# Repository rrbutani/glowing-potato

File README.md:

# glowing-potato

A work in progress. Still needs a name and a README.

##### Group

The group behind this project consists of:
 - [Blake Martini](https://github.com/Dreadzone345)
 - [Sneha Pendharker](https://github.com/spendharkar)
 - [Sameer Mithani](https://github.com/sameermithani)
 - [Rahul Butani](https://github.com/rrbutani)

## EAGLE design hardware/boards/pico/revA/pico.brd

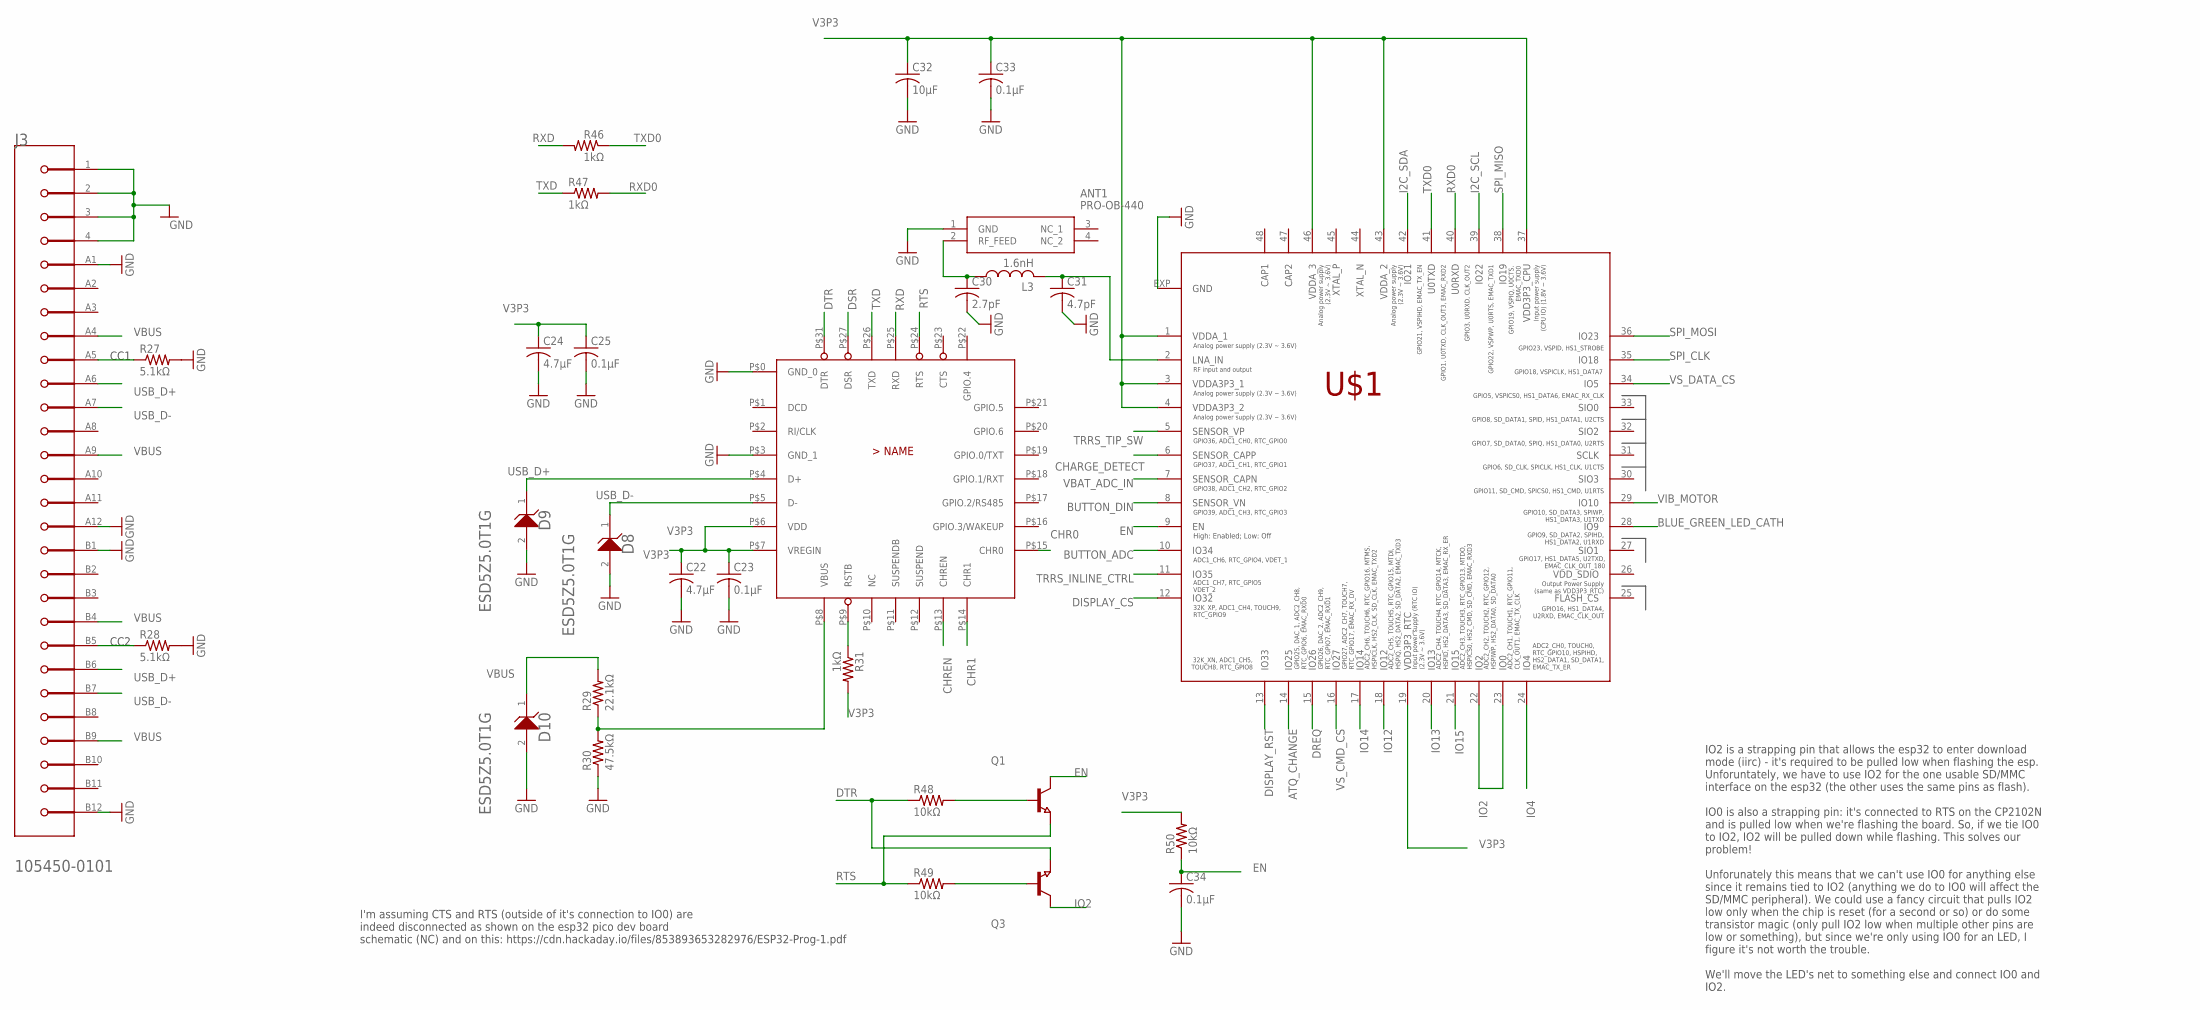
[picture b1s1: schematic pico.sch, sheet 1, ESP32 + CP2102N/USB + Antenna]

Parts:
ANT1: PRO-OB-440; PRO-OB-440_1
C22, C24: 4.7μF; C0402
C23, C25, C33, C34: 0.1μF; C0402
C30: 2.7pF; C0402
C31: 4.7pF; C0402
C32: 10μF; C0402
D8, D9, D10: ON_SEMICONDUCTOR_ESD5Z5.0T1GON_SEMICONDUCTOR_ESD5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; ON_SEMICONDUCTOR_ESD5Z5.0T1G_0
J3: MOLEX_105450-0101MOLEX_105450-0101_0_0; MOLEX_105450-0101_0
JL: CP2102N-A02-GQFN28; QFN28
L3: 1.6nH; R0402
Q1, Q3: NPN-TRANSISTOR_SOT23; SOT23
R27, R28: 5.1kΩ; R0402
R29: 22.1kΩ; R0402
R30: 47.5kΩ; R0402
R31, R46, R47: 1kΩ; R0402
R48, R49, R50: 10kΩ; R0402
U$1: ESP32-PICO-D4; QFN48

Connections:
ATQ_CHANGE: U$1.14 (IO25); also elsewhere on the board
BLUE_GREEN_LED_CATH: U$1.28 (IO9); also elsewhere on the board
BUTTON_ADC: U$1.10 (IO34); also elsewhere on the board
BUTTON_DIN: U$1.8 (SENSOR_VN); also elsewhere on the board
CHARGE_DETECT: U$1.6 (SENSOR_CAPP); also elsewhere on the board
CHR0: JL.P$15 (CHR0)
CHR1: JL.P$14 (CHR1)
CHREN: JL.P$13 (CHREN)
CP_RSTB: JL.P$9 (RSTB), R31.1
DISPLAY_CS: U$1.12 (IO32); also elsewhere on the board
DISPLAY_RST: U$1.13 (IO33); also elsewhere on the board
DREQ: U$1.15 (IO26); also elsewhere on the board
DSR: JL.P$27 (DSR)
DTR: JL.P$31 (DTR), Q3.2 (E), R48.1
EN: C34.1, Q1.3 (C), R50.1, U$1.9 (EN)
GND: ANT1.1 (GND), C22.2, C23.2, C24.2, C25.2, C30.2, C31.2, C32.2, C33.2, C34.2, D8.2 (A), D9.2 (A), D10.2 (A), J3.1 (MNT_1), J3.2 (MNT_2), J3.3 (MNT_3), J3.4 (MNT_4), J3.A1 (1_GND), J3.A12 (2_GND), J3.B1 (3_GND), J3.B12 (4_GND), JL.P$0 (GND_0), JL.P$3 (GND_1), R27.2, R28.2, R30.1, U$1.EXP (GND); also elsewhere on the board
I2C_SCL: U$1.39 (IO22); also elsewhere on the board
I2C_SDA: U$1.42 (IO21); also elsewhere on the board
IO2: Q3.3 (C), U$1.22 (IO2), U$1.23 (IO0); also elsewhere on the board
IO4: U$1.24 (IO4); also elsewhere on the board
IO12: U$1.18 (IO12); also elsewhere on the board
IO13: U$1.20 (IO13); also elsewhere on the board
IO14: U$1.17 (IO14); also elsewhere on the board
IO15: U$1.21 (IO15); also elsewhere on the board
unnamed: ANT1.2 (RF_FEED), C30.1, L3.1
unnamed: C31.1, L3.2, U$1.2 (LNA_IN)
unnamed: J3.A5 (CC1), R27.1
unnamed: J3.B5 (CC2), R28.1
unnamed: JL.P$8 (VBUS), R29.1, R30.2
unnamed: Q1.1 (B), R48.2
unnamed: Q3.1 (B), R49.2
RTS: JL.P$24 (RTS), Q1.2 (E), R49.1
RXD: JL.P$25 (RXD), R46.2
RXD0: R47.2, U$1.40 (U0RXD)
SPI_CLK: U$1.35 (IO18); also elsewhere on the board
SPI_MISO: U$1.38 (IO19); also elsewhere on the board
SPI_MOSI: U$1.36 (IO23); also elsewhere on the board
TRRS_INLINE_CTRL: U$1.11 (IO35); also elsewhere on the board
TRRS_TIP_SW: U$1.5 (SENSOR_VP); also elsewhere on the board
TXD: JL.P$26 (TXD), R47.1
TXD0: R46.1, U$1.41 (U0TXD)
USB_D+: D9.1 (K), J3.A6 (1_D+), J3.B6 (2_D+), JL.P$4 (D+)
USB_D-: D8.1 (K), J3.A7 (1_D-), J3.B7 (2_D-), JL.P$5 (D-)
V3P3: C22.1, C23.1, C24.1, C25.1, C32.1, C33.1, JL.P$6 (VDD), JL.P$7 (VREGIN), R31.2, R50.2, U$1.1 (VDDA_1), U$1.3 (VDDA3P3_1), U$1.4 (VDDA3P3_2), U$1.19 (VDD3P3_RTC), U$1.37 (VDD3P3_CPU), U$1.43 (VDDA_2), U$1.46 (VDDA_3); also elsewhere on the board
VBAT_ADC_IN: U$1.7 (SENSOR_CAPN); also elsewhere on the board
VBUS: D10.1 (K), J3.A4 (1_VBUS), J3.A9 (2_VBUS), J3.B4 (3_VBUS), J3.B9 (4_VBUS), R29.2; also elsewhere on the board
VIB_MOTOR: U$1.29 (IO10); also elsewhere on the board
VS_CMD_CS: U$1.16 (IO27); also elsewhere on the board
VS_DATA_CS: U$1.34 (IO5); also elsewhere on the board

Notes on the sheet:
CC1
CC2
I'm assuming CTS and RTS (outside of it's connection to IO0) are indeed disconnected as shown on the esp32 pico dev board schematic (NC) and on this: https://cdn.hackaday.io/files/853893653282976/ESP32-Prog-1.pdf
IO2 is a strapping pin that allows the esp32 to enter download mode (iirc) - it's required to be pulled low when flashing the esp. Unforuntately, we have to use IO2 for the one usable SD/MMC interface on the esp32 (the other uses the same pins as flash). IO0 is also a strapping pin: it's connected 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

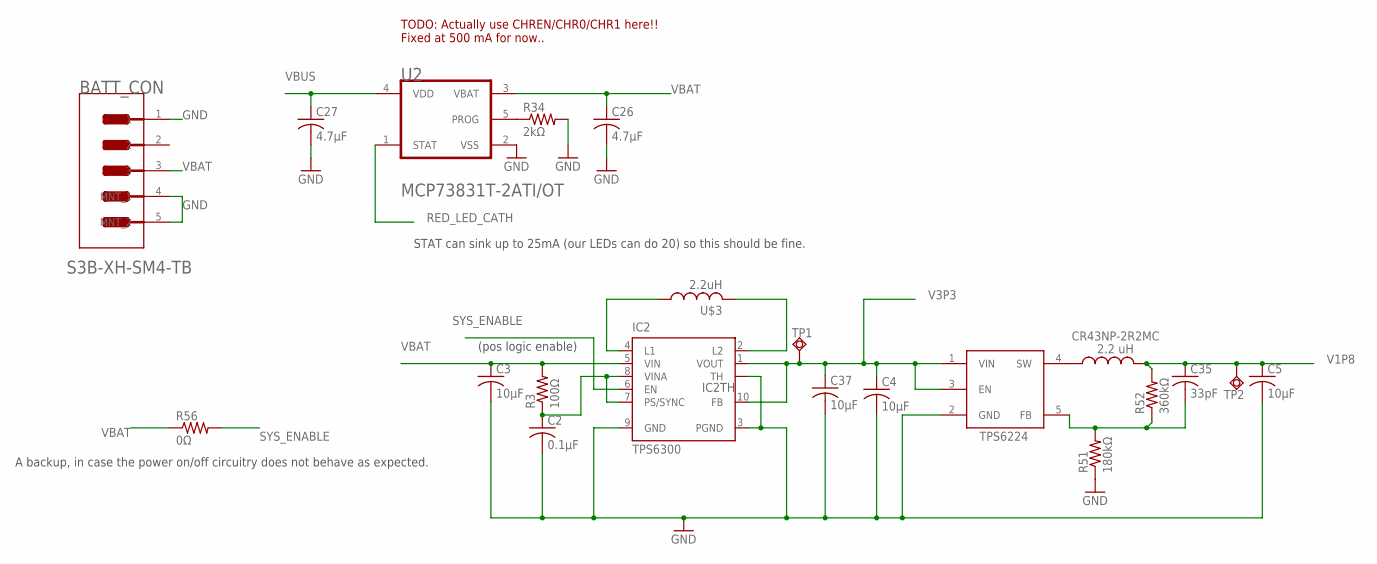
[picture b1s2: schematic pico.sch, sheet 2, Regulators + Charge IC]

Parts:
BATT_CON: JST_S3B-XH-SM4-TBJST_S3B-XH-SM4-TB_0_0; JST_S3B-XH-SM4-TB_0
C2: 0.1μF; C0402
C3, C4, C5, C37: 10μF; C0402
C26, C27: 4.7μF; C0402
C35: 33pF; C0402
IC2: TPS6300; DRC-S-PVSON-N10
R3: 100Ω; R0402
R34: 2kΩ; R0402
R51: 180kΩ; R0402
R52: 360kΩ; R0402
R56: 0Ω; R0603
TP1, TP2: TPSQTP15SQ; TP15SQ
TPS6224: TPS62240; TSP62240
U2: MICROCHIP_MCP73831T-2ATI-OTMICROCHIP_MCP73831T-2A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; MICROCHIP_MCP73831T-2ATI-OT_1
U$3: 2.2uH; INDUCTOR
U$5: CR43NP-2R2MC; INDUCTOR

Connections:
GND: BATT_CON.1, BATT_CON.4 (MNT_1), BATT_CON.5 (MNT_2), C2.2, C3.2, C4.2, C5.2, C26.2, C27.2, C37.2, IC2.3 (PGND), IC2.9 (GND), IC2.TH, R34.2, R51.1, TPS6224.2 (GND), U2.2 (VSS); also elsewhere on the board
unnamed: C2.1, IC2.7 (PS/SYNC), IC2.8 (VINA), R3.1
unnamed: IC2.2 (L2), U$3.P$2 (2)
unnamed: IC2.4 (L1), U$3.P$1 (1)
unnamed: TPS6224.4 (SW), U$5.P$1 (1)
unnamed: C35.2, R51.2, R52.1, TPS6224.5 (FB)
unnamed: R34.1, U2.5 (PROG)
RED_LED_CATH: U2.1 (STAT); also elsewhere on the board
SYS_ENABLE: IC2.6 (EN), R56.2; also elsewhere on the board
V1P8: C5.1, C35.1, R52.2, TP2.TP, U$5.P$2 (2); also elsewhere on the board
V3P3: C4.1, C37.1, IC2.1 (VOUT), IC2.10 (FB), TP1.TP, TPS6224.1 (VIN), TPS6224.3 (EN); also elsewhere on the board
VBAT: BATT_CON.3, C3.1, C26.1, IC2.5 (VIN), R3.2, R56.1, U2.3 (VBAT); also elsewhere on the board
VBUS: C27.1, U2.4 (VDD); also elsewhere on the board

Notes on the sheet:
TPS6224
TODO: Actually use CHREN/CHR0/CHR1 here!! Fixed at 500 mA for now..
STAT can sink up to 25mA (our LEDs can do 20) so this should be fine.
(pos logic enable)
A backup, in case the power on/off circuitry does not behave as expected.

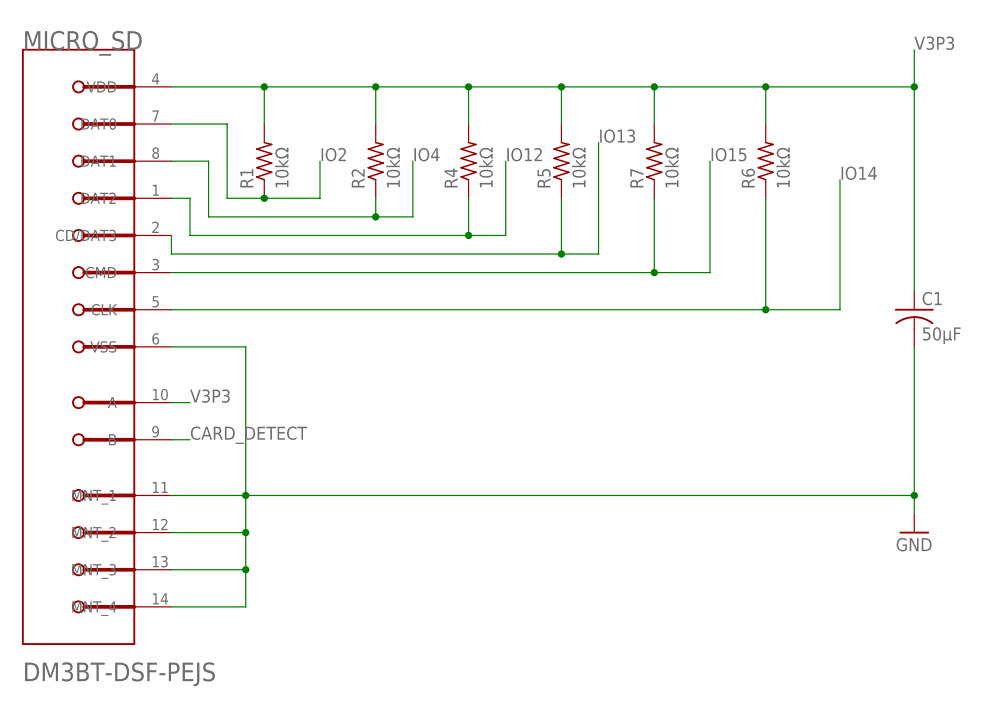
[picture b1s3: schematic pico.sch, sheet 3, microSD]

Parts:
C1: 50μF; C0402
MICRO_SD: HIROSE_DM3BT-DSF-PEJSHIROSE_DM3BT-DSF-PEJS_0_0; HIROSE_DM3BT-DSF-PEJS_0
R1, R2, R4, R5, R6, R7: 10kΩ; R0402

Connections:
CARD_DETECT: MICRO_SD.9 (B); also elsewhere on the board
GND: C1.2, MICRO_SD.6 (VSS), MICRO_SD.11 (MNT_1), MICRO_SD.12 (MNT_2), MICRO_SD.13 (MNT_3), MICRO_SD.14 (MNT_4); also elsewhere on the board
IO2: MICRO_SD.7 (DAT0), R1.1; also elsewhere on the board
IO4: MICRO_SD.8 (DAT1), R2.1; also elsewhere on the board
IO12: MICRO_SD.1 (DAT2), R4.1; also elsewhere on the board
IO13: MICRO_SD.2 (CD/DAT3), R5.1; also elsewhere on the board
IO14: MICRO_SD.5 (CLK), R6.1; also elsewhere on the board
IO15: MICRO_SD.3 (CMD), R7.1; also elsewhere on the board
V3P3: C1.1, MICRO_SD.4 (VDD), MICRO_SD.10 (A), R1.2, R2.2, R4.2, R5.2, R6.2, R7.2; also elsewhere on the board

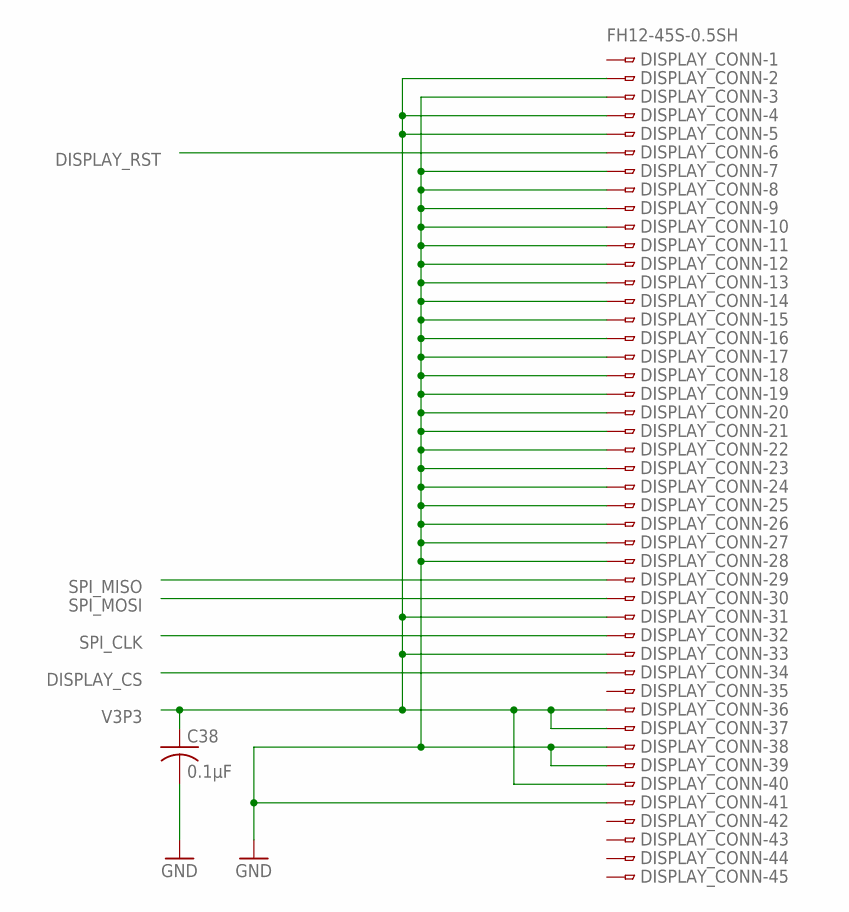
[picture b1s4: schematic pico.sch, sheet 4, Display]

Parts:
C38: 0.1μF; C0402
DISPLAY_CONN: FH12-45S-0.5SH

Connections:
DISPLAY_CS: DISPLAY_CONN.34; also elsewhere on the board
DISPLAY_RST: DISPLAY_CONN.6; also elsewhere on the board
GND: C38.2, DISPLAY_CONN.3, DISPLAY_CONN.7, DISPLAY_CONN.8, DISPLAY_CONN.9, DISPLAY_CONN.10, DISPLAY_CONN.11, DISPLAY_CONN.12, DISPLAY_CONN.13, DISPLAY_CONN.14, DISPLAY_CONN.15, DISPLAY_CONN.16, DISPLAY_CONN.17, DISPLAY_CONN.18, DISPLAY_CONN.19, DISPLAY_CONN.20, DISPLAY_CONN.21, DISPLAY_CONN.22, DISPLAY_CONN.23, DISPLAY_CONN.24, DISPLAY_CONN.25, DISPLAY_CONN.26, DISPLAY_CONN.27, DISPLAY_CONN.28, DISPLAY_CONN.38, DISPLAY_CONN.39, DISPLAY_CONN.41; also elsewhere on the board
SPI_CLK: DISPLAY_CONN.32; also elsewhere on the board
SPI_MISO: DISPLAY_CONN.29; also elsewhere on the board
SPI_MOSI: DISPLAY_CONN.30; also elsewhere on the board
V3P3: C38.1, DISPLAY_CONN.2, DISPLAY_CONN.4, DISPLAY_CONN.5, DISPLAY_CONN.31, DISPLAY_CONN.33, DISPLAY_CONN.36, DISPLAY_CONN.37, DISPLAY_CONN.40; also elsewhere on the board

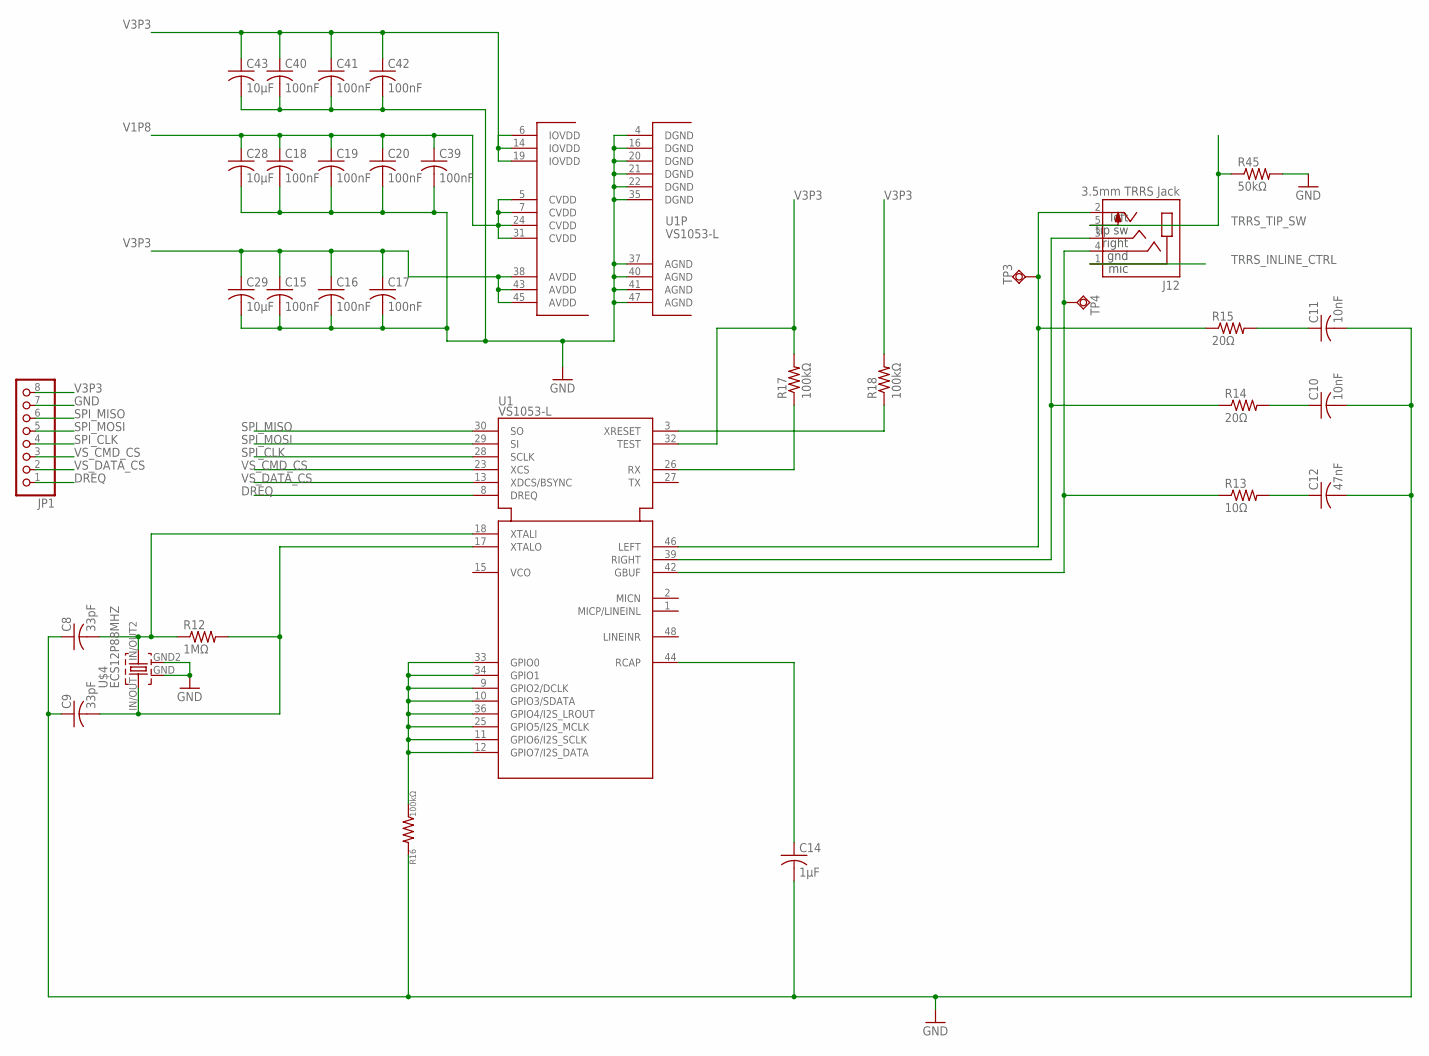
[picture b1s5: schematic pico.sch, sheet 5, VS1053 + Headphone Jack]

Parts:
C8, C9: 33pF; C0402
C10, C11: 10nF; C0402
C12: 47nF; C0402
C14: 1μF; C0402
C15, C16, C17, C18, C19, C20, C39, C40, C41, C42: 100nF; C0402
C28, C29, C43: 10μF; C0402
J12: 3.5mm TRRS Jack; CUI_SJ-43515TS-SMT
JP1: PINHD-1X8LOCK; 1X08-LOCK
R12: 1MΩ; R0402
R13: 10Ω; R0402
R14, R15: 20Ω; R0402
R16, R17, R18: 100kΩ; R0402
R45: 50kΩ; R0402
TP3, TP4: TPSQTP15SQ; TP15SQ
U1: VS1053-L; LQFP48
U$4: ECS12P88MHZ; ECSCRYSTAL

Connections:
DREQ: JP1.1, U1.8 (DREQ); also elsewhere on the board
GND: C8.1, C9.1, C10.2, C11.2, C12.2, C14.2, C15.2, C16.2, C17.2, C18.2, C19.2, C20.2, C28.2, C29.2, C39.2, C40.2, C41.2, C42.2, C43.2, JP1.7, R16.2, R45.2, U1.4 (DGND), U1.16 (DGND), U1.20 (DGND), U1.21 (DGND), U1.22 (DGND), U1.35 (DGND), U1.37 (AGND), U1.40 (AGND), U1.41 (AGND), U1.47 (AGND), U$4.GND, U$4.GND2; also elsewhere on the board
unnamed: C8.2, R12.1, U1.18 (XTALI), U$4.IN/OUT2
unnamed: C9.2, R12.2, U1.17 (XTALO), U$4.IN/OUT
unnamed: R17.1, U1.26 (RX)
unnamed: C12.1, R13.2
unnamed: C10.1, R14.2
unnamed: C11.1, R15.2
unnamed: C14.1, U1.44 (RCAP)
unnamed: R18.1, U1.3 (XRESET)
unnamed: R16.1, U1.9 (GPIO2/DCLK), U1.10 (GPIO3/SDATA), U1.11 (GPIO6/I2S_SCLK), U1.12 (GPIO7/I2S_DATA), U1.25 (GPIO5/I2S_MCLK), U1.33 (GPIO0), U1.34 (GPIO1), U1.36 (GPIO4/I2S_LROUT)
unnamed: J12.4 (RING2), R13.1, TP4.TP, U1.42 (GBUF)
unnamed: J12.3 (RING1), R14.1, U1.39 (RIGHT)
unnamed: J12.2 (TIP), R15.1, TP3.TP, U1.46 (LEFT)
SPI_CLK: JP1.4, U1.28 (SCLK); also elsewhere on the board
SPI_MISO: JP1.6, U1.30 (SO); also elsewhere on the board
SPI_MOSI: JP1.5, U1.29 (SI); also elsewhere on the board
TRRS_INLINE_CTRL: J12.1 (SLEEVE); also elsewhere on the board
TRRS_TIP_SW: J12.5 (TIP_SWITCH), R45.1; also elsewhere on the board
V1P8: C18.1, C19.1, C20.1, C28.1, C39.1, U1.5 (CVDD), U1.7 (CVDD), U1.24 (CVDD), U1.31 (CVDD); also elsewhere on the board
V3P3: C15.1, C16.1, C17.1, C29.1, C40.1, C41.1, C42.1, C43.1, JP1.8, R17.2, R18.2, U1.6 (IOVDD), U1.14 (IOVDD), U1.19 (IOVDD), U1.32 (TEST), U1.38 (AVDD), U1.43 (AVDD), U1.45 (AVDD); also elsewhere on the board
VS_CMD_CS: JP1.3, U1.23 (XCS); also elsewhere on the board
VS_DATA_CS: JP1.2, U1.13 (XDCS/BSYNC); also elsewhere on the board

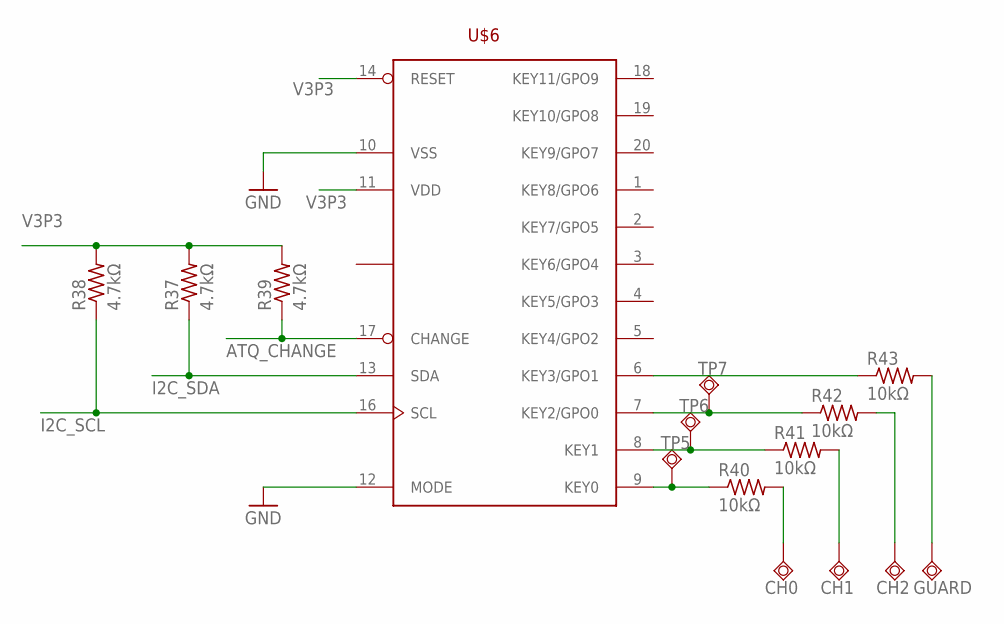
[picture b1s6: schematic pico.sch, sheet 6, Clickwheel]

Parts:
CH0, CH1, CH2: TPSQTP20SQ; TP20SQ
GUARD: TPSQTP20SQ; TP20SQ
R37, R38, R39: 4.7kΩ; R0402
R40, R41, R42, R43: 10kΩ; R0402
TP5, TP6, TP7: TPSQTP15SQ; TP15SQ
U$6: COMMS-AT42QT2120XU; TSSOP20

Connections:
ATQ_CHANGE: R39.1, U$6.17 (CHANGE); also elsewhere on the board
GND: U$6.10 (VSS), U$6.12 (MODE); also elsewhere on the board
I2C_SCL: R38.1, U$6.16 (SCL); also elsewhere on the board
I2C_SDA: R37.1, U$6.13 (SDA); also elsewhere on the board
unnamed: R40.1, TP5.TP, U$6.9 (KEY0)
unnamed: CH1.TP, R41.2
unnamed: CH2.TP, R42.2
unnamed: R41.1, TP6.TP, U$6.8 (KEY1)
unnamed: R42.1, TP7.TP, U$6.7 (KEY2/GPO0)
unnamed: R43.1, U$6.6 (KEY3/GPO1)
unnamed: CH0.TP, R40.2
unnamed: GUARD.TP, R43.2
V3P3: R37.2, R38.2, R39.2, U$6.11 (VDD), U$6.14 (RESET); also elsewhere on the board

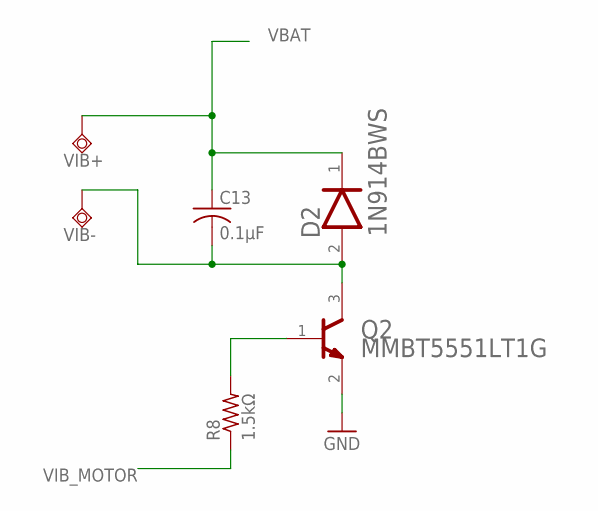
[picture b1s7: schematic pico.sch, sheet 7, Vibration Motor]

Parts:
C13: 0.1μF; C0402
D2: ON_SEMI_1N914BWSON_SEMI_1N914BWS_0_0; ON_SEMI_1N914BWS_0
Q2: ON_SEMI_MMBT5551LT1GON_SEMI_MMBT5551LT1G_0_0; ON_SEMI_MMBT5551LT1G_0
R8: 1.5kΩ; R0402
VIB+: TPSQTP20SQ; TP20SQ
VIB-: TPSQTP20SQ; TP20SQ

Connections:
GND: Q2.2 (EMITTER); also elsewhere on the board
unnamed: C13.2, D2.2 (ANODE), Q2.3 (COLLECTOR), VIB-.TP
unnamed: Q2.1 (BASE), R8.2
VBAT: C13.1, D2.1 (CATHODE), VIB+.TP; also elsewhere on the board
VIB_MOTOR: R8.1; also elsewhere on the board

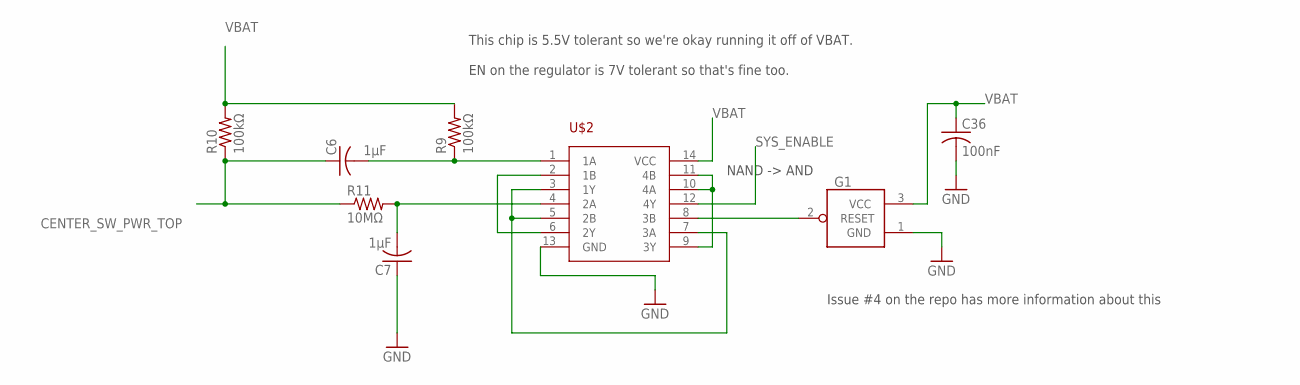
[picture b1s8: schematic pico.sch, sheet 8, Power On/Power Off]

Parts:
C6, C7: 1μF; C0402
C36: 100nF; C0402
G1: APX809S-31SA; SOT23
R9, R10: 100kΩ; R0402
R11: 10MΩ; R0402
U$2: TOSHIBA-NAND-GATE; TSSOP14

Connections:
CENTER_SW_PWR_TOP: C6.1, R10.1, R11.1; also elsewhere on the board
GND: C7.1, C36.2, G1.1 (GND), U$2.13 (GND); also elsewhere on the board
unnamed: C6.2, R9.1, U$2.1 (1A)
unnamed: U$2.3 (1Y), U$2.5 (2B), U$2.7 (3A)
unnamed: C7.2, R11.2, U$2.4 (2A)
unnamed: U$2.2 (1B), U$2.6 (2Y)
unnamed: U$2.9 (3Y), U$2.10 (4A), U$2.11 (4B)
unnamed: G1.2 (RESET), U$2.8 (3B)
SYS_ENABLE: U$2.12 (4Y); also elsewhere on the board
VBAT: C36.1, G1.3 (VCC), R9.2, R10.2, U$2.14 (VCC); also elsewhere on the board

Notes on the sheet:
This chip is 5.5V tolerant so we're okay running it off of VBAT. EN on the regulator is 7V tolerant so that's fine too.
Issue #4 on the repo has more information about this
NAND -> AND

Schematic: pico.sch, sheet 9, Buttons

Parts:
C21: 0.1μF; C0402
CENTER_SW: E-SWITCH_TL3315NF100QE-SWITCH_TL3315NF100Q_0_0; E-SWITCH_TL3315NF100Q_0
CENTER_SW_PWR: E-SWITCH_TL3315NF100QE-SWITCH_TL3315NF100Q_0_0; E-SWITCH_TL3315NF100Q_0
D3, D4, D5, D6, D7: DIODESOD-523; SOD-523
DOWN_SW: E-SWITCH_TL3315NF160QE-SWITCH_TL3315NF160Q_0_0; E-SWITCH_TL3315NF160Q_0
LEFT_SW: E-SWITCH_TL3315NF160QE-SWITCH_TL3315NF160Q_0_0; E-SWITCH_TL3315NF160Q_0
R19: 155kΩ; R0402
R20: 75kΩ; R0402
R21: 35kΩ; R0402
R22: 15kΩ; R0402
R23, R25: 5kΩ; R0402
R24: 50kΩ; R0402
R26: 10kΩ; R0402
R54: 315kΩ; R0402
RIGHT_SW: E-SWITCH_TL3315NF160QE-SWITCH_TL3315NF160Q_0_0; E-SWITCH_TL3315NF160Q_0
UP_SW: E-SWITCH_TL3315NF160QE-SWITCH_TL3315NF160Q_0_0; E-SWITCH_TL3315NF160Q_0

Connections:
BUTTON_ADC: R19.1, R20.1, R21.1, R22.1, R23.1, R25.2, R54.1; also elsewhere on the board
BUTTON_DIN: C21.2, R24.2; also elsewhere on the board
CARD_DETECT: R54.2; also elsewhere on the board
CENTER_SW_PWR_TOP: CENTER_SW_PWR.1, CENTER_SW_PWR.1-2 (1), CENTER_SW_PWR.2, CENTER_SW_PWR.2-2 (2); also elsewhere on the board
GND: CENTER_SW_PWR.3, CENTER_SW_PWR.3-2 (3), CENTER_SW_PWR.4, CENTER_SW_PWR.4-2 (4), R25.1, R26.1; also elsewhere on the board
unnamed: D4.A, R20.2, UP_SW.3, UP_SW.3-2 (3), UP_SW.4, UP_SW.4-2 (4)
unnamed: D5.A, R21.2, RIGHT_SW.3, RIGHT_SW.3-2 (3), RIGHT_SW.4, RIGHT_SW.4-2 (4)
unnamed: D6.A, DOWN_SW.3, DOWN_SW.3-2 (3), DOWN_SW.4, DOWN_SW.4-2 (4), R22.2
unnamed: CENTER_SW.3, CENTER_SW.3-2 (3), CENTER_SW.4, CENTER_SW.4-2 (4), D7.A, R23.2
unnamed: D3.K (C), D4.K (C), D5.K (C), D6.K (C), D7.K (C), R24.1, R26.2
unnamed: D3.A, LEFT_SW.3, LEFT_SW.3-2 (3), LEFT_SW.4, LEFT_SW.4-2 (4), R19.2
V3P3: C21.1, CENTER_SW.1, CENTER_SW.1-2 (1), CENTER_SW.2, CENTER_SW.2-2 (2), DOWN_SW.1, DOWN_SW.1-2 (1), DOWN_SW.2, DOWN_SW.2-2 (2), LEFT_SW.1, LEFT_SW.1-2 (1), LEFT_SW.2, LEFT_SW.2-2 (2), RIGHT_SW.1, RIGHT_SW.1-2 (1), RIGHT_SW.2, RIGHT_SW.2-2 (2), UP_SW.1, UP_SW.1-2 (1), UP_SW.2, UP_SW.2-2 (2); also elsewhere on the board

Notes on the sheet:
We're going to cheat and introduce a second center switch. It's not optimal but it's a lot less risky than hooking up the real center button to VBAT and hoping that the diode brings the voltage down to spec.

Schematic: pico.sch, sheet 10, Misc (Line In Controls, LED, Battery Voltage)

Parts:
D1: BROADCOM_HSMF-C113BROADCOM_HSMF-C113_0_0; BROADCOM_HSMF-C113_0
R32, R44, R53: 10kΩ; R0402
R33: 5kΩ; R0402
R35: 100Ω; R0402
R36: 50Ω; R0402
R55: 25Ω; R0402

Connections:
BLUE_GREEN_LED_CATH: R36.2, R55.2; also elsewhere on the board
CHARGE_DETECT: R53.1; also elsewhere on the board
GND: R32.1; also elsewhere on the board
unnamed: D1.1 (BLUE_CATHODE), R55.1
unnamed: D1.3 (RED_CATHODE), R35.1
unnamed: D1.4 (GREEN_CATHODE), R36.1
RED_LED_CATH: R35.2, R53.2; also elsewhere on the board
TRRS_INLINE_CTRL: R44.1; also elsewhere on the board
V3P3: D1.2 (COMMON_ANODE), R44.2; also elsewhere on the board
VBAT: R33.2; also elsewhere on the board
VBAT_ADC_IN: R32.2, R33.1; also elsewhere on the board

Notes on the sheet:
Red LED has a 1.9V drop and 20mA, so: 1.4V for 20mA = V / I = R = 1.4V / 20mA = 70 ohms since we don't want to blind people let's call it an even 100
Green LED (AlInGaP Green on the C113) has a drop of about 2.3 volts also on about 20mA. 1.0 volts for 20mA = V / I = R = 1 / 20mA = 50 ohms
Blue has a voltage drop of ~3.7V which is greater than our regulated voltage so we won't bother with a current limiting resistor. Actually we'll add one to protect the esp.
I'm not sure this will work, so leave this resistor off initially/until we've thought it through.
(resistor value here is a guess)

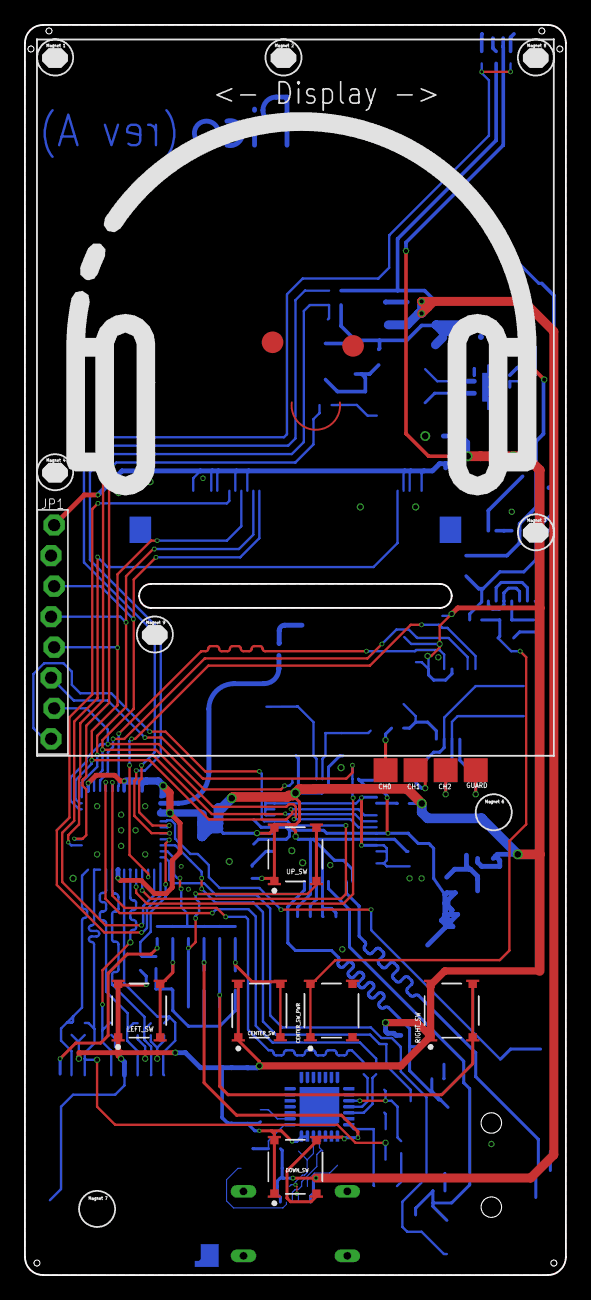
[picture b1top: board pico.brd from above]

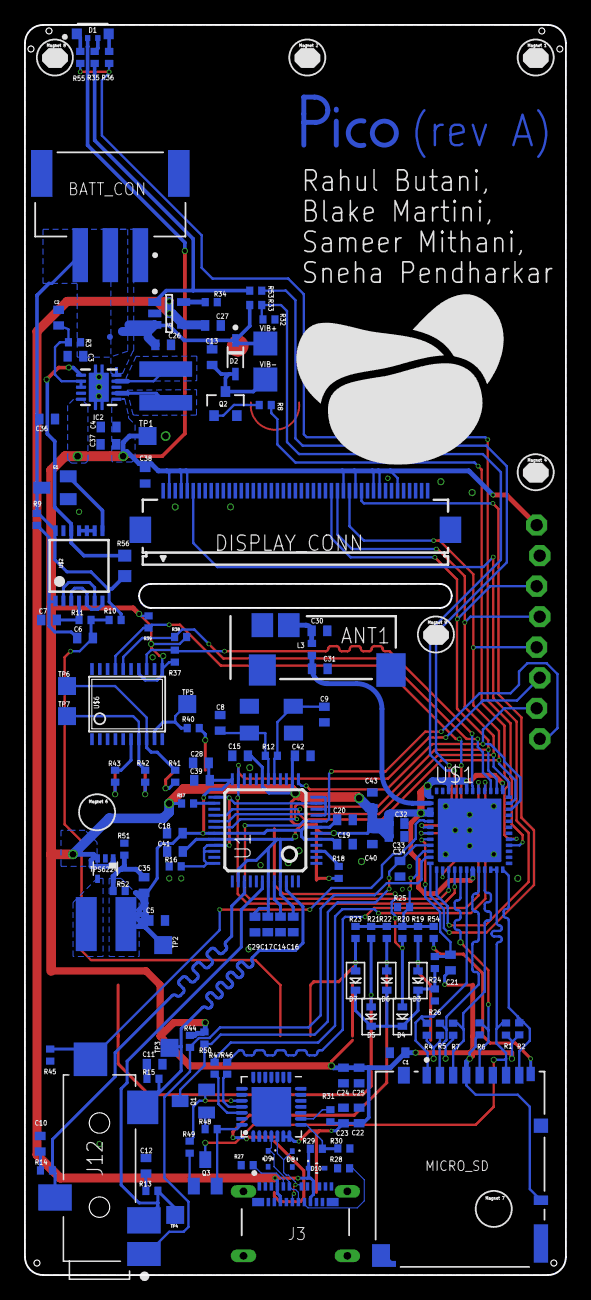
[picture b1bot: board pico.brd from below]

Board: 2 copper layers, 45.0 x 104.0 mm, 151 parts (140 on the bottom side), 94 nets.

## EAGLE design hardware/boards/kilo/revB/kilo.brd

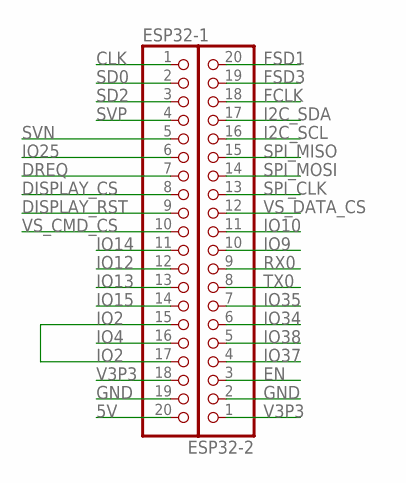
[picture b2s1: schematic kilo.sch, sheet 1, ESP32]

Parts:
ESP32-1, ESP32-2: PINHD-1X20; 1X20

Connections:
5V: ESP32-1.20
CLK: ESP32-1.1
DISPLAY_CS: ESP32-1.8; also elsewhere on the board
DISPLAY_RST: ESP32-1.9; also elsewhere on the board
DREQ: ESP32-1.7; also elsewhere on the board
EN: ESP32-2.3
FCLK: ESP32-2.18
FSD1: ESP32-2.20
FSD3: ESP32-2.19
GND: ESP32-1.19, ESP32-2.2; also elsewhere on the board
I2C_SCL: ESP32-2.16
I2C_SDA: ESP32-2.17
IO2: ESP32-1.15, ESP32-1.17; also elsewhere on the board
IO4: ESP32-1.16; also elsewhere on the board
IO9: ESP32-2.10; also elsewhere on the board
IO10: ESP32-2.11; also elsewhere on the board
IO12: ESP32-1.12; also elsewhere on the board
IO13: ESP32-1.13; also elsewhere on the board
IO14: ESP32-1.11; also elsewhere on the board
IO15: ESP32-1.14; also elsewhere on the board
IO25: ESP32-1.6; also elsewhere on the board
IO34: ESP32-2.6
IO35: ESP32-2.7
IO37: ESP32-2.4; also elsewhere on the board
IO38: ESP32-2.5; also elsewhere on the board
RX0: ESP32-2.9
SD0: ESP32-1.2
SD2: ESP32-1.3
SPI_CLK: ESP32-2.13; also elsewhere on the board
SPI_MISO: ESP32-2.15; also elsewhere on the board
SPI_MOSI: ESP32-2.14; also elsewhere on the board
SVN: ESP32-1.5
SVP: ESP32-1.4; also elsewhere on the board
TX0: ESP32-2.8
V3P3: ESP32-1.18, ESP32-2.1; also elsewhere on the board
VS_CMD_CS: ESP32-1.10; also elsewhere on the board
VS_DATA_CS: ESP32-2.12; also elsewhere on the board

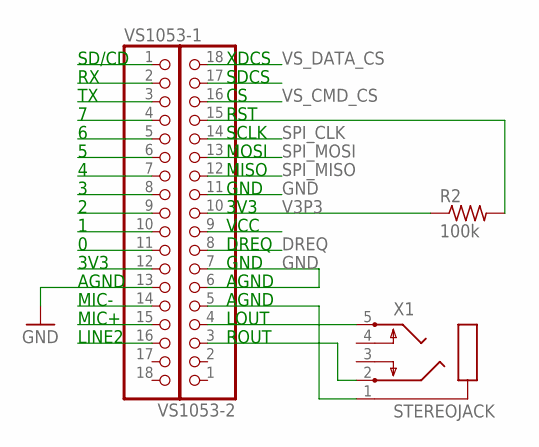
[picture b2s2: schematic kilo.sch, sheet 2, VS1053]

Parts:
R2: 100k; 0207/10
VS1053-1, VS1053-2: PINHD-1X18; 1X18
X1: STEREOJACK; STX3100

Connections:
DREQ: VS1053-2.8; also elsewhere on the board
GND: VS1053-1.13, VS1053-2.6, VS1053-2.7, VS1053-2.11; also elsewhere on the board
unnamed: VS1053-2.4, X1.5
unnamed: VS1053-2.3, X1.2
unnamed: R2.2, VS1053-2.15
unnamed: VS1053-2.5, X1.1
SPI_CLK: VS1053-2.14; also elsewhere on the board
SPI_MISO: VS1053-2.12; also elsewhere on the board
SPI_MOSI: VS1053-2.13; also elsewhere on the board
V3P3: R2.1, VS1053-2.10; also elsewhere on the board
VS_CMD_CS: VS1053-2.16; also elsewhere on the board
VS_DATA_CS: VS1053-2.18; also elsewhere on the board

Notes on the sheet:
LINE2
MIC+
MIC-
AGND
3V3
SD/CD
ROUT
LOUT
GND
DREQ
VCC
MISO
MOSI
SCLK
RST
SDCS
XDCS

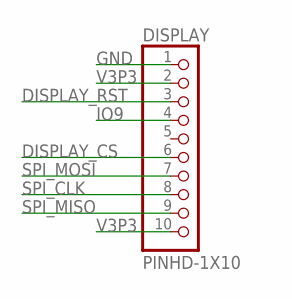
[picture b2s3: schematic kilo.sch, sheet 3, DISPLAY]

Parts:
DISPLAY: PINHD-1X10; 1X10-BIG

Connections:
DISPLAY_CS: DISPLAY.6; also elsewhere on the board
DISPLAY_RST: DISPLAY.3; also elsewhere on the board
GND: DISPLAY.1; also elsewhere on the board
IO9: DISPLAY.4; also elsewhere on the board
SPI_CLK: DISPLAY.8; also elsewhere on the board
SPI_MISO: DISPLAY.9; also elsewhere on the board
SPI_MOSI: DISPLAY.7; also elsewhere on the board
V3P3: DISPLAY.2, DISPLAY.10; also elsewhere on the board

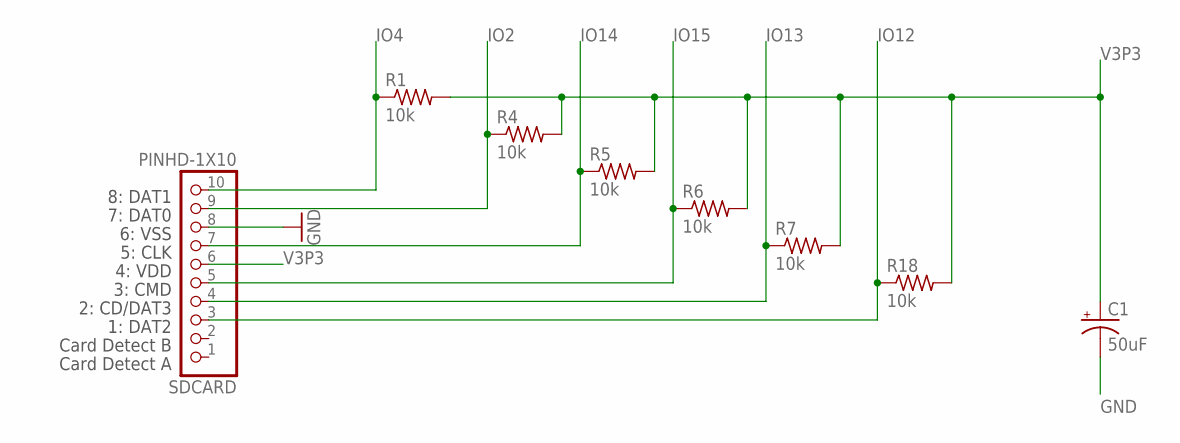
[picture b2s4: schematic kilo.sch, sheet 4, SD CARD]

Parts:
C1: 50uF; E2,5-7
R1, R4, R5, R6, R7, R18: 10k; 0207/10
SDCARD: PINHD-1X10; 1X10-BIG

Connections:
GND: C1.-, SDCARD.8; also elsewhere on the board
IO2: R4.1, SDCARD.9; also elsewhere on the board
IO4: R1.1, SDCARD.10; also elsewhere on the board
IO12: R18.1, SDCARD.3; also elsewhere on the board
IO13: R7.1, SDCARD.4; also elsewhere on the board
IO14: R5.1, SDCARD.7; also elsewhere on the board
IO15: R6.1, SDCARD.5; also elsewhere on the board
V3P3: C1.+, R1.2, R4.2, R5.2, R6.2, R7.2, R18.2, SDCARD.6; also elsewhere on the board

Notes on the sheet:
Card Detect A
Card Detect B
1: DAT2
2: CD/DAT3
3: CMD
4: VDD
5: CLK
6: VSS
7: DAT0
8: DAT1

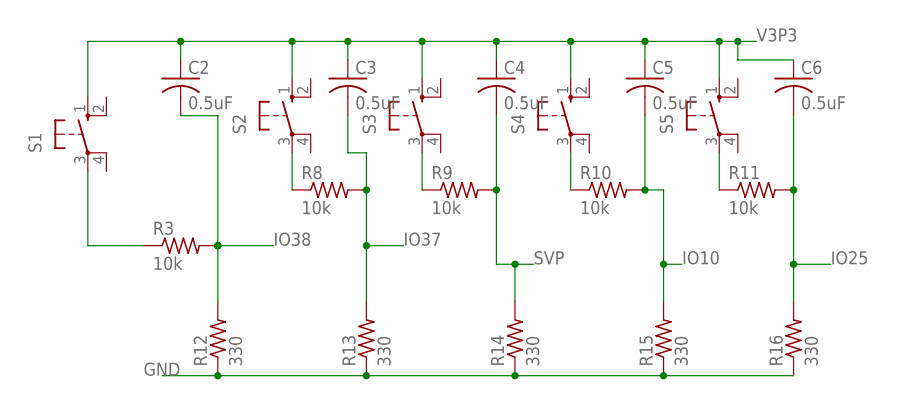
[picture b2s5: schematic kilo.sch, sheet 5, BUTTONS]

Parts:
C2, C3, C4, C5, C6: 0.5uF; C025-024X044
R3, R8, R9, R10, R11: 10k; 0207/10
R12, R13, R14, R15, R16: 330; 0207/10
S1, S2, S3, S4, S5: 10-XX; B3F-10XX

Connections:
GND: R12.1, R13.1, R14.1, R15.1, R16.1; also elsewhere on the board
IO10: C5.2, R10.2, R15.2; also elsewhere on the board
IO25: C6.2, R11.2, R16.2; also elsewhere on the board
IO37: C3.2, R8.2, R13.2; also elsewhere on the board
IO38: C2.2, R3.2, R12.2; also elsewhere on the board
unnamed: R3.1, S1.3
unnamed: R8.1, S2.3
unnamed: R9.1, S3.3
unnamed: R10.1, S4.3
unnamed: R11.1, S5.3
SVP: C4.2, R9.2, R14.2; also elsewhere on the board
V3P3: C2.1, C3.1, C4.1, C5.1, C6.1, S1.1 (S), S2.1 (S), S3.1 (S), S4.1 (S), S5.1 (S); also elsewhere on the board
